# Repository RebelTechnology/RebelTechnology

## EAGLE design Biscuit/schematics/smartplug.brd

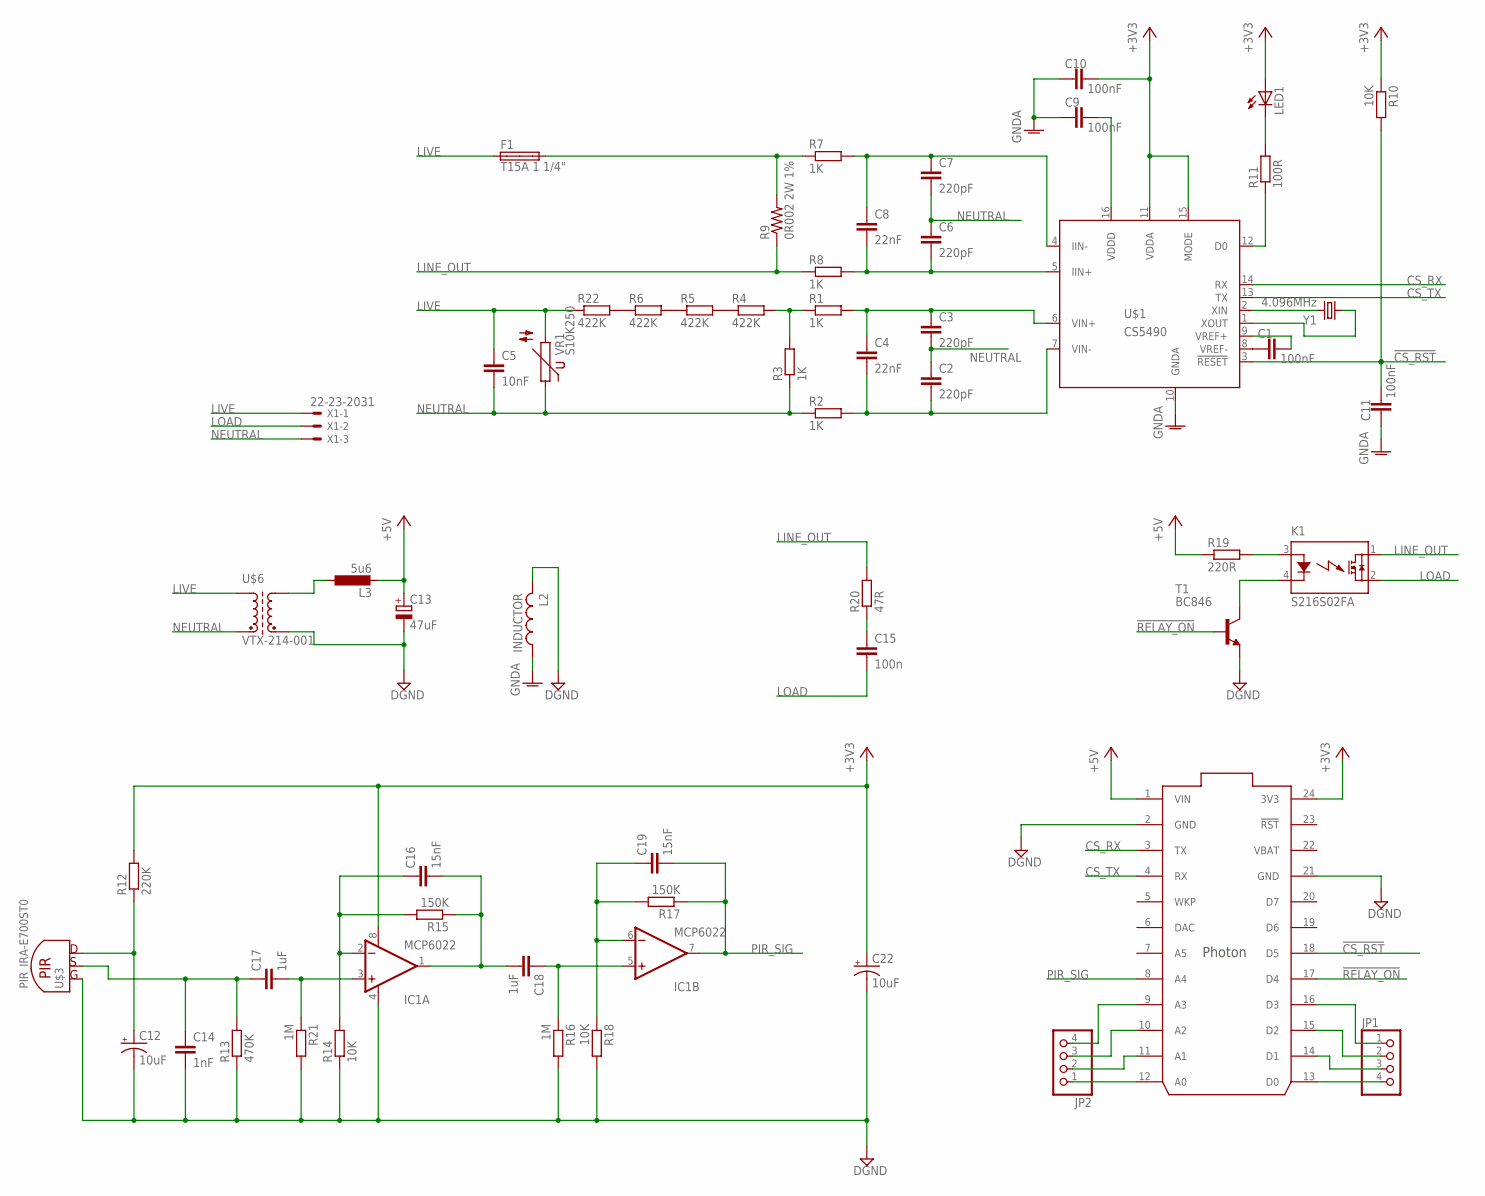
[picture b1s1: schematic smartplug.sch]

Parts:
C1, C9, C10, C11: 100nF; 0603-CAP
C2, C3, C6, C7: 220pF; 0603-CAP
C4, C8: 22nF; 0603-CAP
C5: 10nF; 0603-CAP
C12, C22: 10uF; EIA3216
C13: 47uF; 153CLV-0505
C14: 1nF; 0603-CAP
C15: 100n; C150-054X183
C16, C19: 15nF; 0603-CAP
C17, C18: 1uF; 0603-CAP
F1: T15A 1 1/4"; SH32
IC1: MCP6022; SO08
JP1, JP2: PINHD-1X4; 1X04
K1: S216S02FA; S216S02F
L2: INDUCTOR; 0603
L3: 5u6; ELLCTP
LED1: LEDCHIPLED_1206; CHIPLED_1206
R1, R2, R3, R7, R8: 1K; 0603
R4, R5, R6, R22: 422K; 0603
R9: 0R002 2W 1%; R2512
R10, R14, R18: 10K; 0603
R11: 100R; 0603
R12: 220K; 0603
R13: 470K; 0603
R15, R17: 150K; 0603
R16, R21: 1M; 0603
R19: 220R; 0603
R20: 47R; 0617V
T1: BC846; SOT23
U$1: CS5490; SOIC16N
U$2: PHOTON_WITH_HEADERS; PHOTON
U$3: PIR_IRA-E700ST0
U$6: VTX-214-001
VR1: S10K250
X1: 22-23-2031
Y1: 4.096MHz; CRYSTAL-SMD-10.5X4.8-2PIN

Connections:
!CS_RST: C11.2, R10.2, U$1.3 (!RESET), U$2.18 (D5)
!RELAY_ON: T1.1 (B), U$2.17 (D4)
+3V3: C10.2, C22.A (+), IC1.8 (V+), LED1.A, R10.1, R12.2, U$1.11 (VDDA), U$1.15 (MODE), U$2.24 (3V3)
+5V: C13.+, L3.2, R19.1, U$2.1 (VIN)
CS_RX: U$1.14 (RX), U$2.3 (TX)
CS_TX: U$1.13 (TX), U$2.4 (RX)
DGND: C12.C (-), C13.-, C14.2, C22.C (-), IC1.4 (V-), L2.2, R13.1, R14.1, R16.2, R18.2, R21.2, T1.2 (E), U$2.2 (GND), U$2.21 (GND), U$3.GND, U$6.P$V- (E2)
GNDA: C9.1, C10.1, C11.1, L2.1, U$1.10 (GNDA)
LINE_OUT: K1.1 (DS1), R8.1, R9.1, R20.2
LIVE: C5.1, F1.1A, R22.1, U$6.P$L (A1), VR1.2, X1.1
LOAD: C15.2, K1.2 (DS2), X1.2
unnamed: U$1.2 (XIN), Y1.P$2 (2)
unnamed: U$1.1 (XOUT), Y1.P$1 (1)
unnamed: C1.1, U$1.8 (VREF-)
unnamed: C1.2, U$1.9 (VREF+)
unnamed: C9.2, U$1.16 (VDDD)
unnamed: C12.A (+), R12.1, U$3.DRAIN+ (DRAIN)
unnamed: C2.2, C4.2, R2.2, U$1.7 (VIN-)
unnamed: C3.1, C4.1, R1.2, U$1.6 (VIN+)
unnamed: C6.2, C8.2, R8.2, U$1.5 (IIN+)
unnamed: C7.1, C8.1, R7.2, U$1.4 (IIN-)
unnamed: R1.1, R3.2, R4.2
unnamed: C14.1, C17.1, R13.2, U$3.SOURCE
unnamed: R4.1, R5.2
unnamed: R5.1, R6.2
unnamed: C16.1, IC1.2 (-IN), R14.2, R15.2
unnamed: R11.1, U$1.12 (D0)
unnamed: K1.4 (K), T1.3 (C)
unnamed: C17.2, IC1.3 (+IN), R21.1
unnamed: LED1.C, R11.2
unnamed: C18.1, IC1.5 (+IN), R16.1
unnamed: L3.1, U$6.P$V+ (A2)
unnamed: K1.3 (A), R19.2
unnamed: C15.1, R20.1
unnamed: C19.1, IC1.6 (-IN), R17.2, R18.1
unnamed: C16.2, C18.2, IC1.1 (OUT), R15.1
unnamed: F1.2A, R7.1, R9.2
unnamed: JP2.1, U$2.12 (A0)
unnamed: JP2.2, U$2.11 (A1)
unnamed: JP2.3, U$2.10 (A2)
unnamed: JP2.4, U$2.9 (A3)
unnamed: JP1.4, U$2.13 (D0)
unnamed: JP1.3, U$2.14 (D1)
unnamed: JP1.2, U$2.15 (D2)
unnamed: JP1.1, U$2.16 (D3)
unnamed: R6.1, R22.2
NEUTRAL: C2.1, C3.2, C5.2, C6.1, C7.2, R2.1, R3.1, U$6.P$N (E1), VR1.1, X1.3
PIR_SIG: C19.2, IC1.7 (OUT), R17.1, U$2.8 (A4)
VBAT: U$2.22 (VBAT)

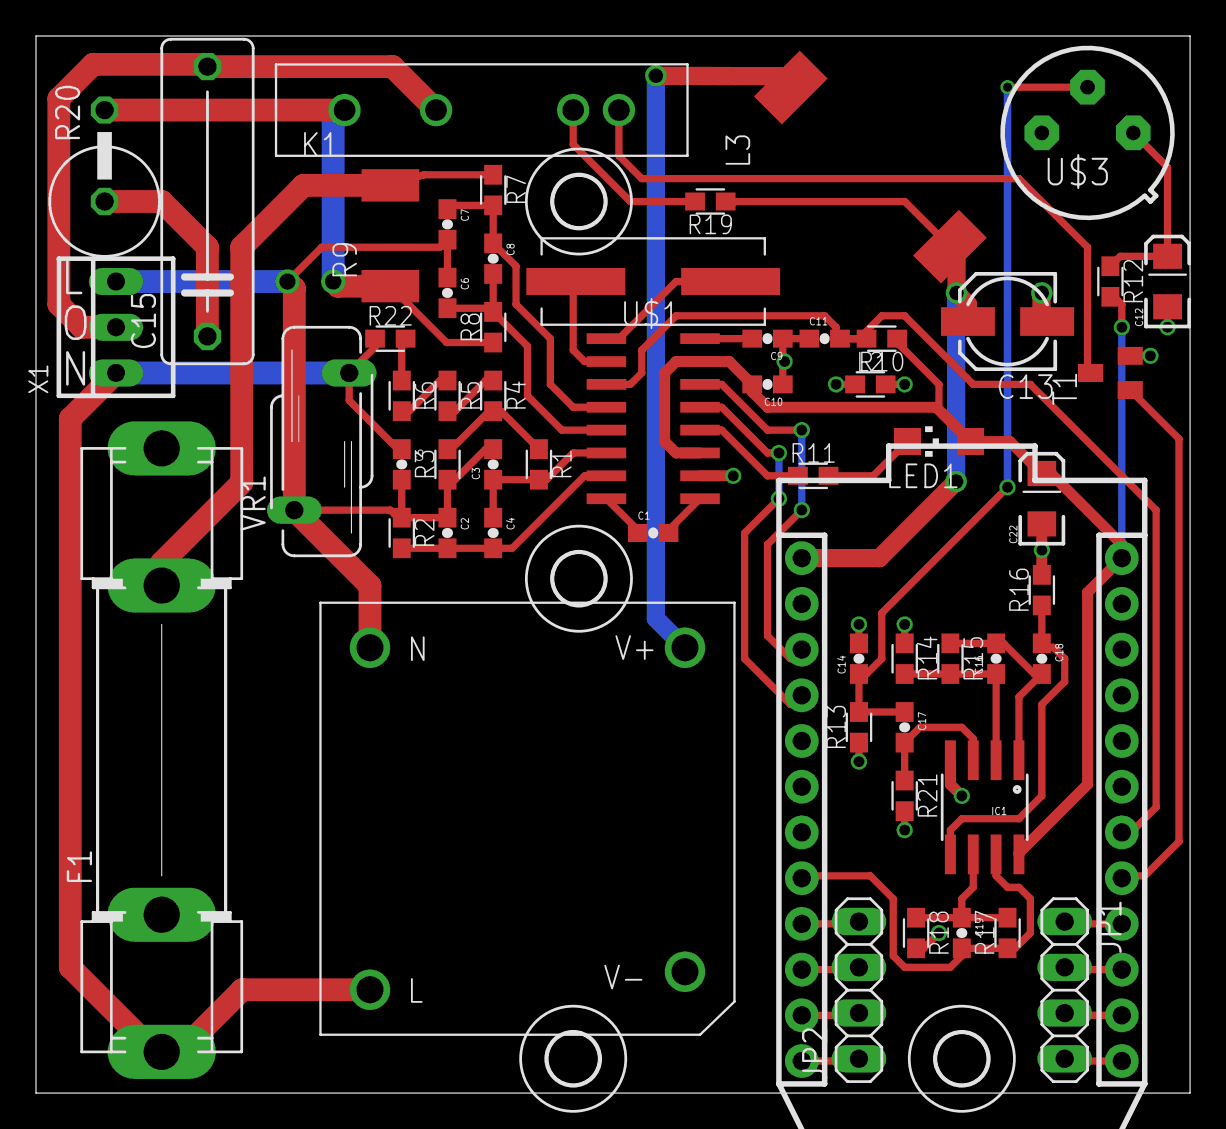
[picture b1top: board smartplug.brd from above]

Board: 2 copper layers, 64.1 x 58.7 mm, 62 parts (0 on the bottom side), 48 nets.

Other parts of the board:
U$4, U$5, U$7, U$8: 2,8

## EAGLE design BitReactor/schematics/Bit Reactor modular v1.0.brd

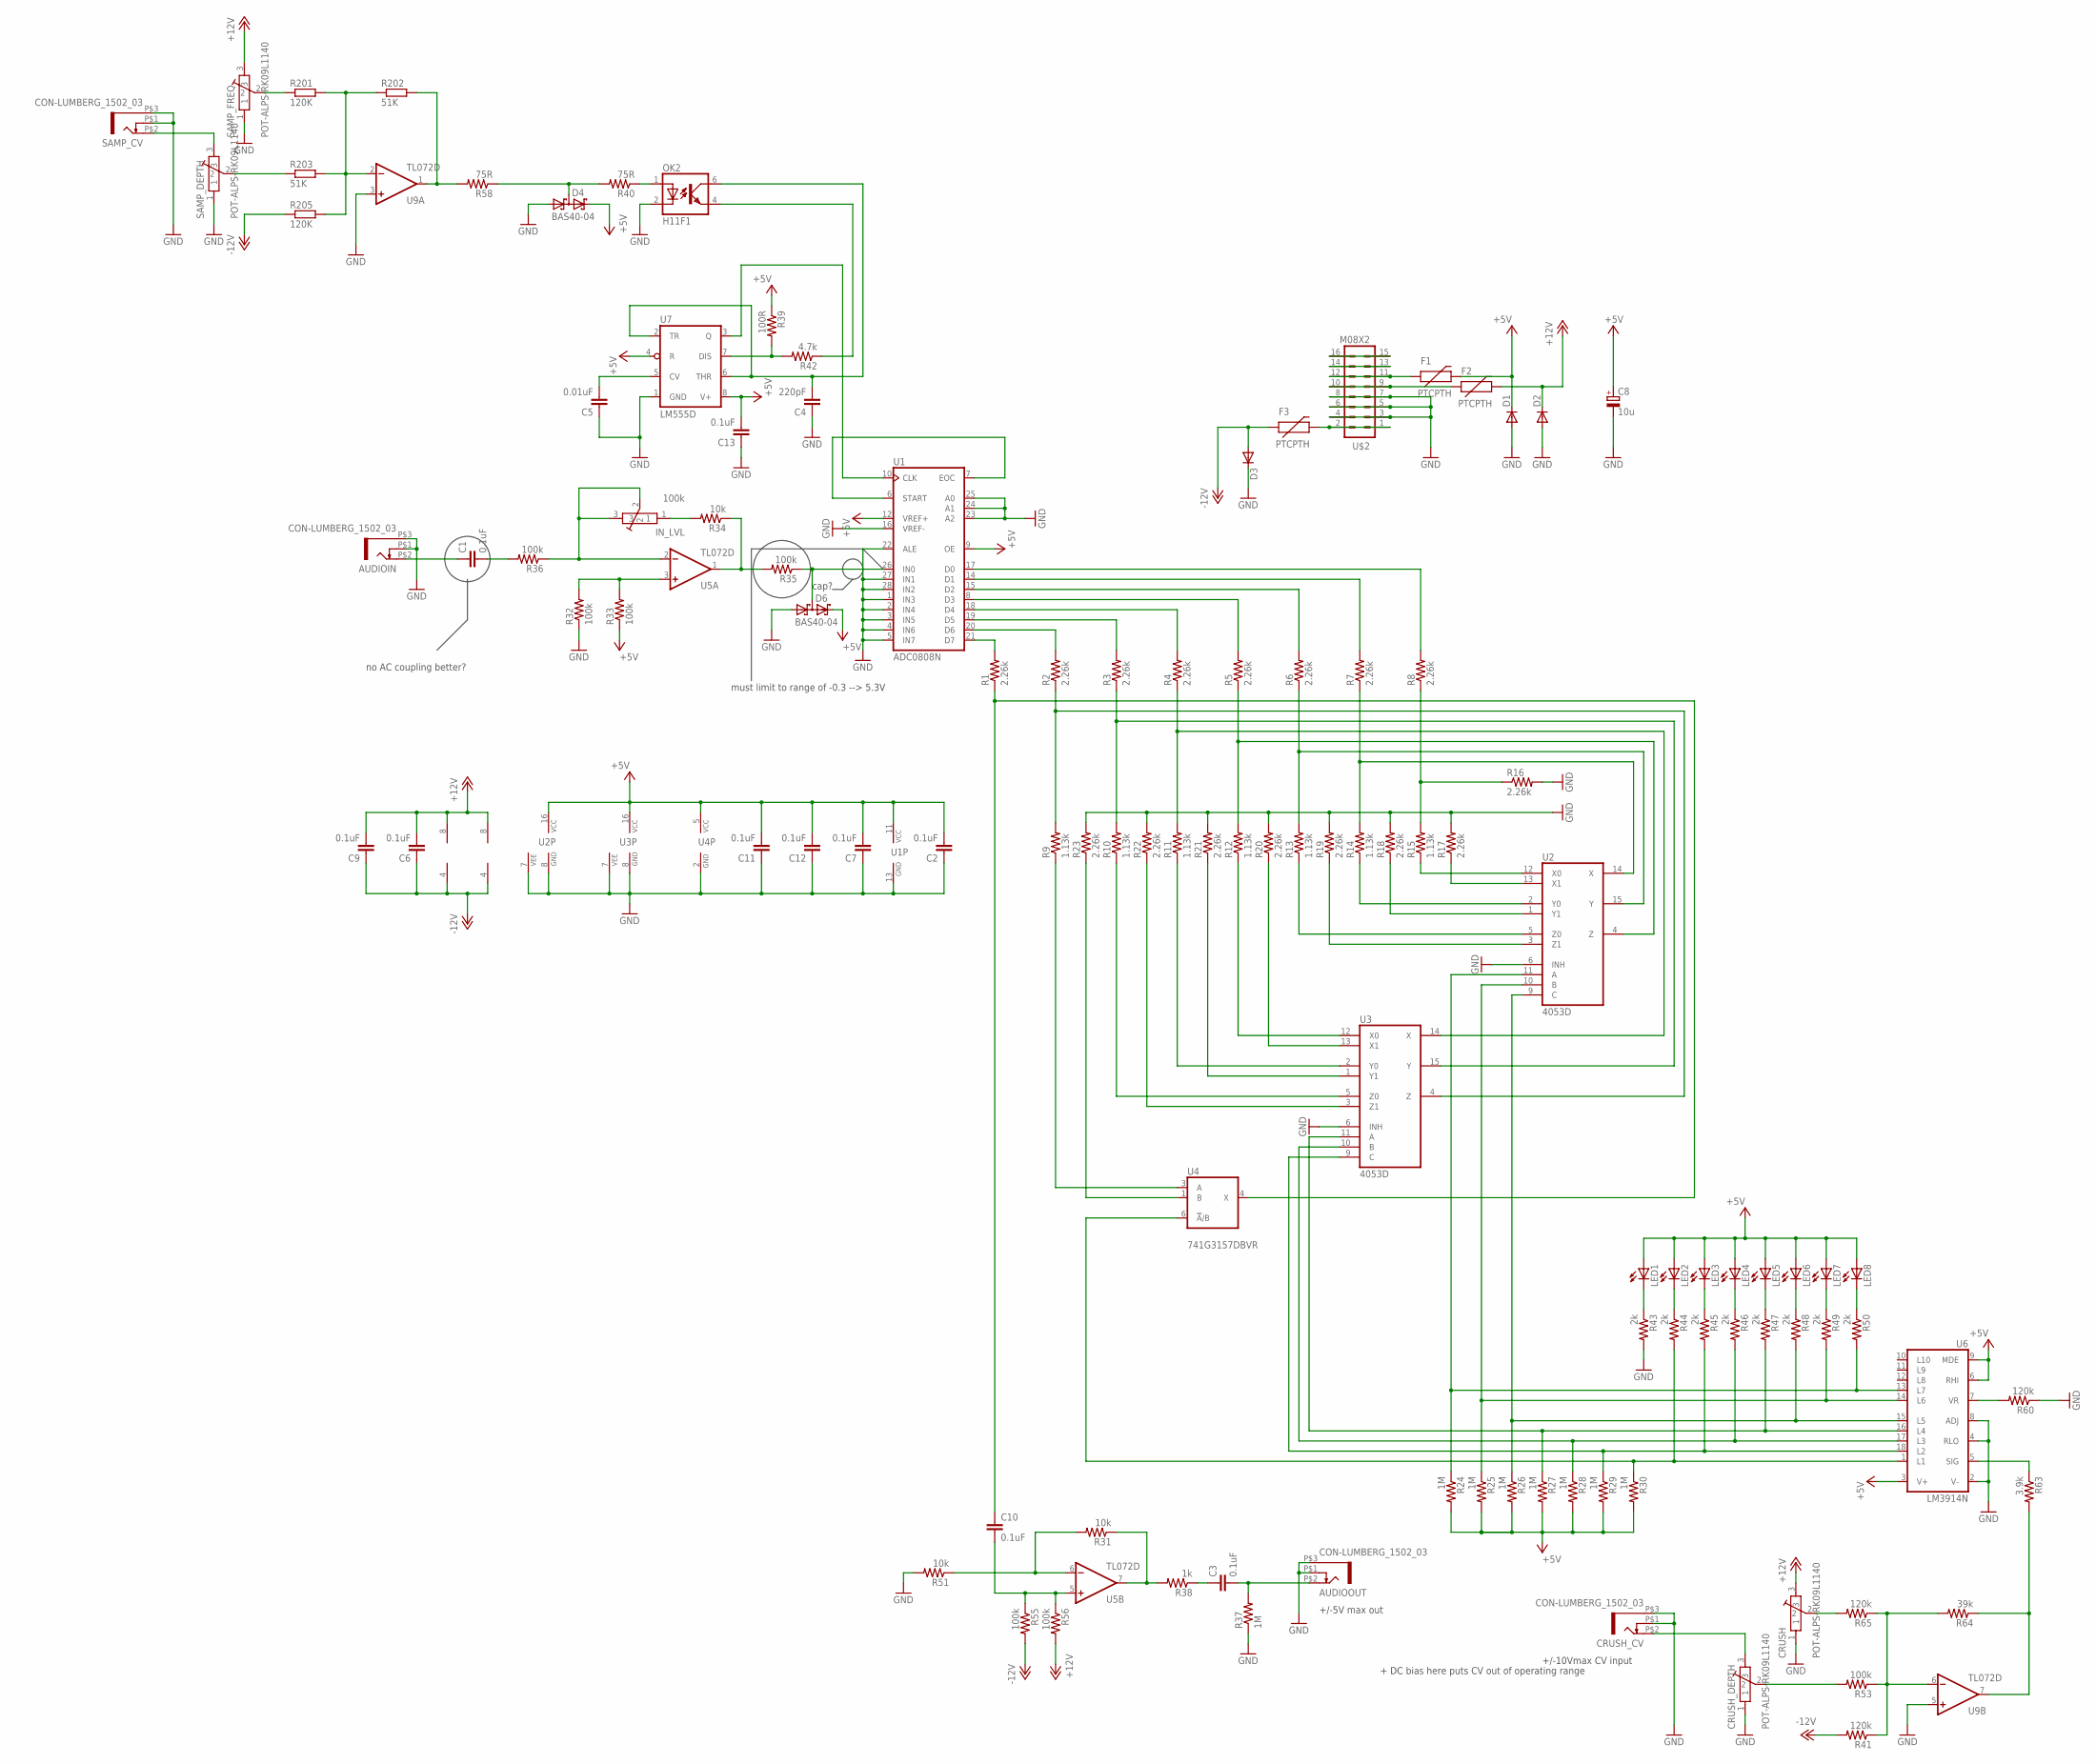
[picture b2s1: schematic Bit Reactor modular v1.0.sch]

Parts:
AUDIOIN: CON-LUMBERG_1502_03
AUDIOOUT: CON-LUMBERG_1502_03
C1, C2, C6, C7, C9, C10, C11, C12, C13: 0.1uF; C025-030X050
C3: 0.1uF; C025-025X050
C4: 220pF; C025-030X050
C5: 0.01uF; C025-030X050
C8: 10u; E5-6
CRUSH: POT-ALPS-RK09L1140
CRUSH_CV: CON-LUMBERG_1502_03
CRUSH_DEPTH: POT-ALPS-RK09L1140
D1, D2, D3: DIODE1N4001; DIODE-1N4001
D4, D6: BAS40-04; SOT23
F1, F2, F3: PTCPTH; PTC
IN_LVL: 100k; POT-ALPS-RK09L1140
LED1, LED2, LED3, LED4, LED5, LED6, LED7, LED8: LED3MM
OK2: H11F1; DIL05
R1, R2, R3, R4, R5, R6, R7, R8, R16, R17, R18, R19, R20, R21, R22, R23: 2.26k; R0805W
R9, R10, R11, R12, R13, R14, R15: 1.13k; R0805W
R24, R25, R26, R27, R28, R29, R30, R37: 1M; R0402
R31, R34, R51: 10k; 0207/10
R32, R33, R35, R36, R53, R55, R56: 100k; 0207/10
R38: 1k; 0207/10
R39: 100R; 0207/10
R40, R58: 75R; 0207/10
R41, R60, R65: 120k; 0207/10
R42: 4.7k; 0207/10
R43, R44, R45, R46, R47, R49, R50: 2k; 0207/7
R48: 2k; 0207/10
R63: 3.9k; 0207/10
R64: 39k; 0207/10
R201, R205: 120K; 0204/7
R202, R203: 51K; 0204/7
SAMP_CV: CON-LUMBERG_1502_03
SAMP_DEPTH: POT-ALPS-RK09L1140
SAMP_FREQ: POT-ALPS-RK09L1140
U1: ADC0808N; DIL28-6
U2, U3: 4053D; SO16
U4: 741G3157DBVR; DBV_R-PDSO-G6
U5, U9: TL072D; SO08
U6: LM3914N; DIL18
U7: LM555D; SO08
U$2: M08X2; 2X8

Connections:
+5V: C2.2, C7.2, C8.+, C11.2, C12.2, C13.2, D1.C, D4.2 (C2), D6.2 (C2), F1.P$2 (2), LED1.A, LED2.A, LED3.A, LED4.A, LED5.A, LED6.A, LED7.A, LED8.A, R24.2, R25.2, R26.2, R27.2, R28.2, R29.2, R30.2, R33.1, R39.1, U1.9 (OE), U1.11 (VCC), U1.12 (VREF+), U2.16 (VCC), U3.16 (VCC), U4.5 (VCC), U6.3 (V+), U6.6 (RHI), U6.9 (MDE), U7.4 (R), U7.8 (V+)
+12V: C6.2, C9.2, CRUSH.3, D2.C, F2.P$2 (2), R56.2, SAMP_FREQ.3, U5.8 (V+), U9.8 (V+)
-12V: C6.1, C9.1, D3.A, F3.P$1 (1), R41.2, R55.2, R205.1, U5.4 (V-), U9.4 (V-)
CV2IN: R63.2, R64.1, U9.7 (OUT)
GND: AUDIOIN.P$1 (4), AUDIOIN.P$3 (5), AUDIOOUT.P$1 (4), AUDIOOUT.P$3 (5), C2.1, C4.1, C5.1, C7.1, C8.-, C11.1, C12.1, C13.1, CRUSH.1, CRUSH_CV.P$1 (4), CRUSH_CV.P$3 (5), CRUSH_DEPTH.1, D1.A, D2.A, D3.C, D4.1 (A1), D6.1 (A1), OK2.2 (C), R16.2, R17.2, R18.2, R19.2, R20.2, R21.2, R22.2, R23.2, R32.1, R37.1, R43.2, R51.2, R60.1, SAMP_CV.P$1 (4), SAMP_CV.P$3 (5), SAMP_DEPTH.1, SAMP_FREQ.1, U1.1 (IN3), U1.2 (IN4), U1.3 (IN5), U1.4 (IN6), U1.5 (IN7), U1.13 (GND), U1.16 (VREF-), U1.22 (ALE), U1.23 (A2), U1.24 (A1), U1.25 (A0), U1.27 (IN1), U1.28 (IN2), U2.6 (INH), U2.7 (VEE), U2.8 (GND), U3.6 (INH), U3.7 (VEE), U3.8 (GND), U4.2 (GND), U6.2 (V-), U6.4 (RLO), U6.8 (ADJ), U7.1 (GND), U9.3 (+IN), U9.5 (+IN), U$2.3, U$2.4, U$2.5, U$2.6, U$2.7, U$2.8
unnamed: R1.2, U1.21 (D7)
unnamed: R2.2, U1.20 (D6)
unnamed: R3.2, U1.19 (D5)
unnamed: R4.2, U1.18 (D4)
unnamed: R5.2, U1.8 (D3)
unnamed: R6.2, U1.15 (D2)
unnamed: R7.2, U1.14 (D1)
unnamed: R8.2, U1.17 (D0)
unnamed: R2.1, R9.2, U3.4 (Z)
unnamed: R3.1, R10.2, U3.15 (Y)
unnamed: R4.1, R11.2, U3.14 (X)
unnamed: R5.1, R12.2, U2.4 (Z)
unnamed: R12.1, U3.12 (X0)
unnamed: R11.1, U3.2 (Y0)
unnamed: R10.1, U3.5 (Z0)
unnamed: R9.1, U4.3 (A)
unnamed: R15.1, U2.12 (X0)
unnamed: R8.1, R15.2, R16.1
unnamed: R17.1, U2.13 (X1)
unnamed: IN_LVL.1, R34.2
unnamed: R14.1, U2.2 (Y0)
unnamed: R13.1, U2.5 (Z0)
unnamed: R18.1, U2.1 (Y1)
unnamed: R19.1, U2.3 (Z1)
unnamed: R20.1, U3.13 (X1)
unnamed: R21.1, U3.1 (Y1)
unnamed: R22.1, U3.3 (Z1)
unnamed: C10.1, R1.1, U4.4 (X)
unnamed: OK2.1 (A), R40.1
unnamed: U$2.13, U$2.14
unnamed: R30.1, R44.2, U4.6 (!A!/B), U6.1 (L1)
unnamed: R29.1, R45.2, U3.9 (C), U6.18 (L2)
unnamed: R28.1, R46.2, U3.10 (B), U6.17 (L3)
unnamed: R27.1, R47.2, U3.11 (A), U6.16 (L4)
unnamed: R26.1, R48.2, U2.9 (C), U6.15 (L5)
unnamed: R25.1, R49.2, U2.10 (B), U6.14 (L6)
unnamed: R24.1, R50.2, U2.11 (A), U6.13 (L7)
unnamed: R34.1, R35.2, U5.1 (OUT)
unnamed: R32.2, R33.2, U5.3 (+IN)
unnamed: IN_LVL.2, IN_LVL.3, R36.1, U5.2 (-IN)
unnamed: F1.P$1 (1), U$2.11, U$2.12
unnamed: C1.2, R36.2
unnamed: R31.1, R38.2, U5.7 (OUT)
unnamed: C3.1, R38.1
unnamed: U1.6 (START), U1.7 (EOC)
unnamed: AUDIOIN.P$2 (3), C1.1
unnamed: CRUSH_DEPTH.2, R53.2
unnamed: CRUSH_CV.P$2 (3), CRUSH_DEPTH.3
unnamed: R39.2, R42.2, U7.7 (DIS)
unnamed: F2.P$1 (1), U$2.9, U$2.10
unnamed: C5.2, U7.5 (CV)
unnamed: LED1.K (C), R43.1
unnamed: U1.10 (CLK), U7.3 (Q)
unnamed: R31.2, R51.1, U5.6 (-IN)
unnamed: LED2.K (C), R44.1
unnamed: LED3.K (C), R45.1
unnamed: LED4.K (C), R46.1
unnamed: LED5.K (C), R47.1
unnamed: LED6.K (C), R48.1
unnamed: LED7.K (C), R49.1
unnamed: LED8.K (C), R50.1
unnamed: D6.3 (C1A2), R35.1, U1.26 (IN0)
unnamed: R7.1, R14.2, U2.14 (X)
unnamed: R6.1, R13.2, U2.15 (Y)
unnamed: C10.2, R55.1, R56.1, U5.5 (+IN)
unnamed: R23.1, U4.1 (B)
unnamed: F3.P$2 (2), U$2.1, U$2.2
unnamed: R201.2, R202.1, R203.2, R205.2, U9.2 (-IN)
unnamed: R201.1, SAMP_FREQ.2
unnamed: R58.2, R202.2, U9.1 (OUT)
unnamed: R203.1, SAMP_DEPTH.2
unnamed: SAMP_CV.P$2 (3), SAMP_DEPTH.3
unnamed: R60.2, U6.7 (VR)
unnamed: R63.1, U6.5 (SIG)
unnamed: R41.1, R53.1, R64.2, R65.1, U9.6 (-IN)
unnamed: D4.3 (C1A2), R40.2, R58.1
unnamed: CRUSH.2, R65.2
OUT: AUDIOOUT.P$2 (3), C3.2, R37.2
PWR_BUS: U$2.15, U$2.16
Y: OK2.4 (EMIT), R42.1
Z: C4.2, OK2.6 (COL), U7.2 (TR), U7.6 (THR)

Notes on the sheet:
+/-10Vmax CV input
+ DC bias here puts CV out of operating range
+/-5V max out
must limit to range of -0.3 --> 5.3V
cap?
no AC coupling better?

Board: 2 copper layers, 111 parts (0 on the bottom side), 86 nets, no tracks yet.

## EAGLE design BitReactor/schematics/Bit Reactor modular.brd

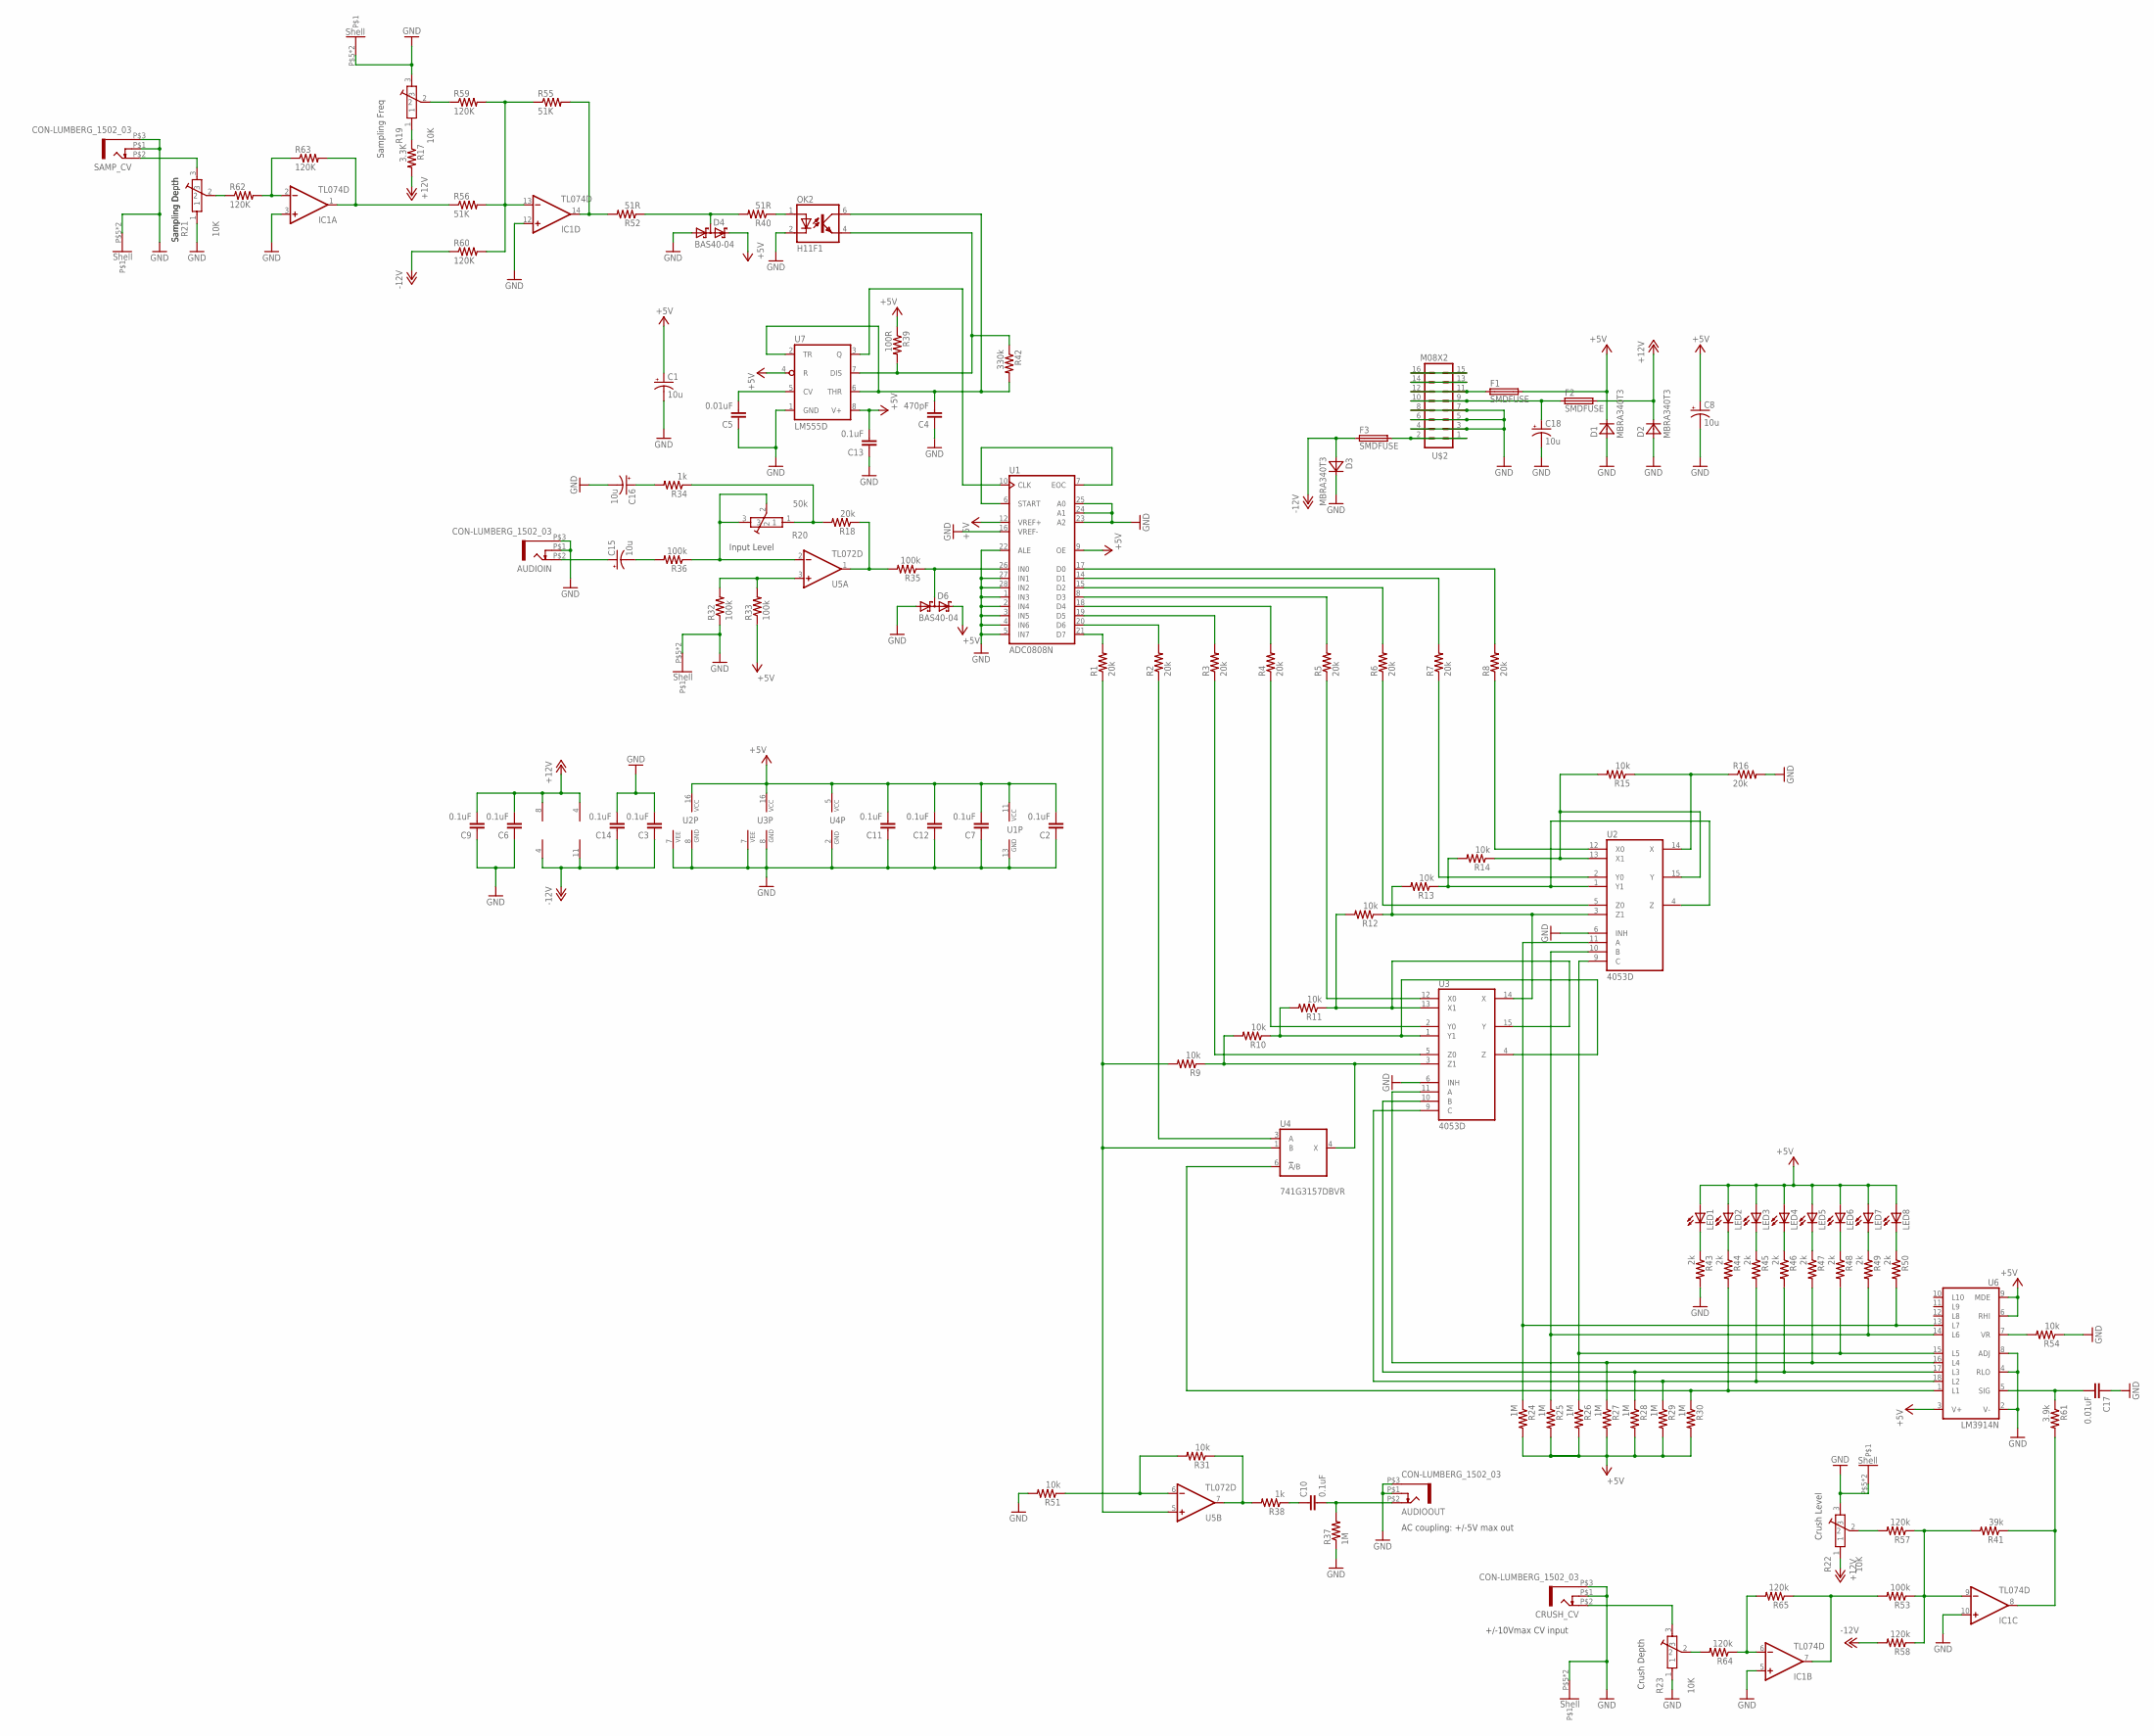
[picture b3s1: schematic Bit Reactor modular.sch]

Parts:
AUDIOIN: CON-LUMBERG_1502_03
AUDIOOUT: CON-LUMBERG_1502_03
C1, C8, C15, C16, C18: 10u; E2-5
C2, C3, C6, C7, C9, C10, C11, C12, C13, C14: 0.1uF; C0402
C4: 470pF; C0402
C5, C17: 0.01uF; C0402
CRUSH_CV: CON-LUMBERG_1502_03
D1, D2, D3: MBRA340T3; SMA
D4, D6: BAS40-04; SOT23
F1, F2, F3: SMDFUSE; 1206
IC1: TL074D; SO14
LED1, LED2, LED3, LED4, LED5, LED6, LED7, LED8: LED3MM
OK2: H11F1; DIL05
R1, R2, R3, R4, R5, R6, R7, R8, R16, R18: 20k; R0805
R9, R10, R11, R12, R13, R14, R15, R54: 10k; R0805
R17: 3.3K; R0805
R19, R21, R22, R23: 10K; POT-ALPS-RK09L1140
R20: 50k; POT-ALPS-RK09L1140
R24, R25, R26, R27, R28, R29, R30, R37: 1M; R0402
R31, R51: 10k; R0402
R32, R33, R35, R36, R53: 100k; R0402
R34, R38: 1k; R0805
R39: 100R; R1206
R40, R52: 51R; R1206
R41: 39k; R0402
R42: 330k; R0402
R43, R44, R45, R46, R47, R48, R49, R50: 2k; R0402
R55, R56: 51K; R0402
R57, R58, R64, R65: 120k; R0402
R59, R60, R62, R63: 120K; R0402
R61: 3.9k; R0402
SAMP_CV: CON-LUMBERG_1502_03
U1: ADC0808N; DIL28-6
U2, U3: 4053D; SO16
U4: 741G3157DBVR; DBV_R-PDSO-G6
U5: TL072D; SO08
U6: LM3914N; DIL18
U7: LM555D; SO08
U$2: M08X2; 2X8

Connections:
+5V: C1.+, C2.2, C7.2, C8.+, C11.2, C12.2, C13.2, D1.C, D4.2 (C2), D6.2 (C2), F1.2, LED1.A, LED2.A, LED3.A, LED4.A, LED5.A, LED6.A, LED7.A, LED8.A, R24.2, R25.2, R26.2, R27.2, R28.2, R29.2, R30.2, R33.1, R39.1, U1.9 (OE), U1.11 (VCC), U1.12 (VREF+), U2.16 (VCC), U3.16 (VCC), U4.5 (VCC), U6.3 (V+), U6.6 (RHI), U6.9 (MDE), U7.4 (R), U7.8 (V+)
+12V: C6.2, C9.2, D2.C, F2.2, IC1.4 (V+), R17.2, R22.1, U5.8 (V+)
-12V: C3.1, C14.1, D3.A, F3.1, IC1.11 (V-), R58.2, R60.1, U5.4 (V-)
CV2IN: IC1.8 (OUT), R41.1, R61.2
GND: AUDIOIN.P$1 (4), AUDIOIN.P$3 (5), AUDIOOUT.P$1 (4), AUDIOOUT.P$3 (5), C1.-, C2.1, C3.2, C4.1, C5.1, C6.1, C7.1, C8.-, C9.1, C11.1, C12.1, C13.1, C14.2, C16.-, C17.1, C18.-, CRUSH_CV.P$1 (4), CRUSH_CV.P$3 (5), D1.A, D2.A, D3.C, D4.1 (A1), D6.1 (A1), IC1.3 (+IN), IC1.5 (+IN), IC1.10 (+IN), IC1.12 (+IN), OK2.2 (C), R16.2, R19.3, R19.P$5, R19.P$6, R20.P$5, R20.P$6, R21.1, R21.P$5, R21.P$6, R22.3, R22.P$5, R22.P$6, R23.1, R23.P$5, R23.P$6, R32.1, R37.1, R43.2, R51.2, R54.1, SAMP_CV.P$1 (4), SAMP_CV.P$3 (5), U1.1 (IN3), U1.2 (IN4), U1.3 (IN5), U1.4 (IN6), U1.5 (IN7), U1.13 (GND), U1.16 (VREF-), U1.22 (ALE), U1.23 (A2), U1.24 (A1), U1.25 (A0), U1.27 (IN1), U1.28 (IN2), U2.6 (INH), U2.7 (VEE), U2.8 (GND), U3.6 (INH), U3.7 (VEE), U3.8 (GND), U4.2 (GND), U6.2 (V-), U6.4 (RLO), U6.8 (ADJ), U7.1 (GND), U$2.3, U$2.4, U$2.5, U$2.6, U$2.7, U$2.8
unnamed: R1.2, U1.21 (D7)
unnamed: R2.2, U1.20 (D6)
unnamed: R3.2, U1.19 (D5)
unnamed: R4.2, U1.18 (D4)
unnamed: R5.2, U1.8 (D3)
unnamed: R6.2, U1.15 (D2)
unnamed: R7.2, U1.14 (D1)
unnamed: R8.2, U1.17 (D0)
unnamed: R17.1, R19.1
unnamed: AUDIOIN.P$2 (3), C15.+
unnamed: C15.-, R36.2
unnamed: R13.1, R14.2, U2.1 (Y1), U2.4 (Z)
unnamed: R5.1, U3.12 (X0)
unnamed: R4.1, U3.2 (Y0)
unnamed: R3.1, U3.5 (Z0)
unnamed: R2.1, U4.3 (A)
unnamed: R8.1, U2.12 (X0)
unnamed: R21.2, R62.1
unnamed: IC1.2 (-IN), R62.2, R63.1
unnamed: R18.2, R20.1, R34.1
unnamed: R7.1, U2.2 (Y0)
unnamed: R6.1, U2.5 (Z0)
unnamed: IC1.1 (OUT), R56.1, R63.2
unnamed: R12.1, R13.2, U2.3 (Z1), U3.14 (X)
unnamed: R11.1, R12.2, U3.13 (X1), U3.15 (Y)
unnamed: R10.1, R11.2, U3.1 (Y1), U3.4 (Z)
unnamed: R9.1, R10.2, U3.3 (Z1), U4.4 (X)
unnamed: R1.1, R9.2, U4.1 (B), U5.5 (+IN)
unnamed: OK2.1 (A), R40.1
unnamed: U$2.13, U$2.14
unnamed: R30.1, R44.2, U4.6 (!A!/B), U6.1 (L1)
unnamed: R29.1, R45.2, U3.9 (C), U6.18 (L2)
unnamed: R28.1, R46.2, U3.10 (B), U6.17 (L3)
unnamed: R27.1, R47.2, U3.11 (A), U6.16 (L4)
unnamed: R26.1, R48.2, U2.9 (C), U6.15 (L5)
unnamed: R25.1, R49.2, U2.10 (B), U6.14 (L6)
unnamed: R24.1, R50.2, U2.11 (A), U6.13 (L7)
unnamed: R18.1, R35.2, U5.1 (OUT)
unnamed: R32.2, R33.2, U5.3 (+IN)
unnamed: R20.2, R20.3, R36.1, U5.2 (-IN)
unnamed: F1.1, U$2.11, U$2.12
unnamed: R23.2, R64.2
unnamed: R31.1, R38.2, U5.7 (OUT)
unnamed: C10.1, R38.1
unnamed: U1.6 (START), U1.7 (EOC)
unnamed: IC1.6 (-IN), R64.1, R65.2
unnamed: CRUSH_CV.P$2 (3), R23.3
unnamed: IC1.7 (OUT), R53.2, R65.1
unnamed: C18.+, F2.1, U$2.9, U$2.10
unnamed: C5.2, U7.5 (CV)
unnamed: LED1.K (C), R43.1
unnamed: U1.10 (CLK), U7.3 (Q)
unnamed: R31.2, R51.1, U5.6 (-IN)
unnamed: LED2.K (C), R44.1
unnamed: LED3.K (C), R45.1
unnamed: LED4.K (C), R46.1
unnamed: LED5.K (C), R47.1
unnamed: LED6.K (C), R48.1
unnamed: LED7.K (C), R49.1
unnamed: LED8.K (C), R50.1
unnamed: D6.3 (C1A2), R35.1, U1.26 (IN0)
unnamed: R14.1, R15.2, U2.13 (X1), U2.15 (Y)
unnamed: C16.+, R34.2
unnamed: F3.2, U$2.1, U$2.2
unnamed: IC1.13 (-IN), R55.1, R56.2, R59.2, R60.2
unnamed: R19.2, R59.1
unnamed: IC1.14 (OUT), R52.2, R55.2
unnamed: R21.3, SAMP_CV.P$2 (3)
unnamed: R54.2, U6.7 (VR)
unnamed: C17.2, R61.1, U6.5 (SIG)
unnamed: IC1.9 (-IN), R41.2, R53.1, R57.1, R58.1
unnamed: D4.3 (C1A2), R40.2, R52.1
unnamed: R22.2, R57.2
unnamed: R15.1, R16.1, U2.14 (X)
OUT: AUDIOOUT.P$2 (3), C10.2, R37.2
PWR_BUS: U$2.15, U$2.16
Y: OK2.4 (EMIT), R39.2, R42.1, U7.7 (DIS)
Z: C4.2, OK2.6 (COL), R42.2, U7.2 (TR), U7.6 (THR)

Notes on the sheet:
+/-10Vmax CV input
AC coupling: +/-5V max out
Sampling Depth
Sampling Freq
Input Level
Crush Depth
Crush Level

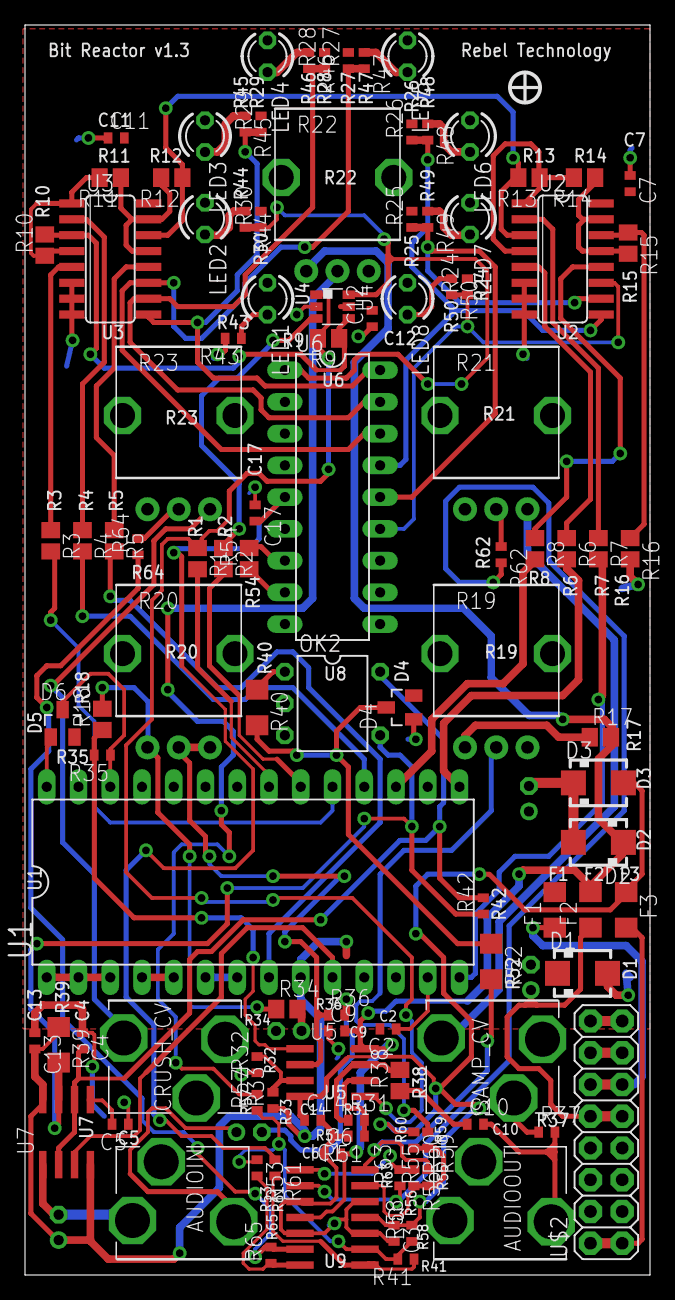
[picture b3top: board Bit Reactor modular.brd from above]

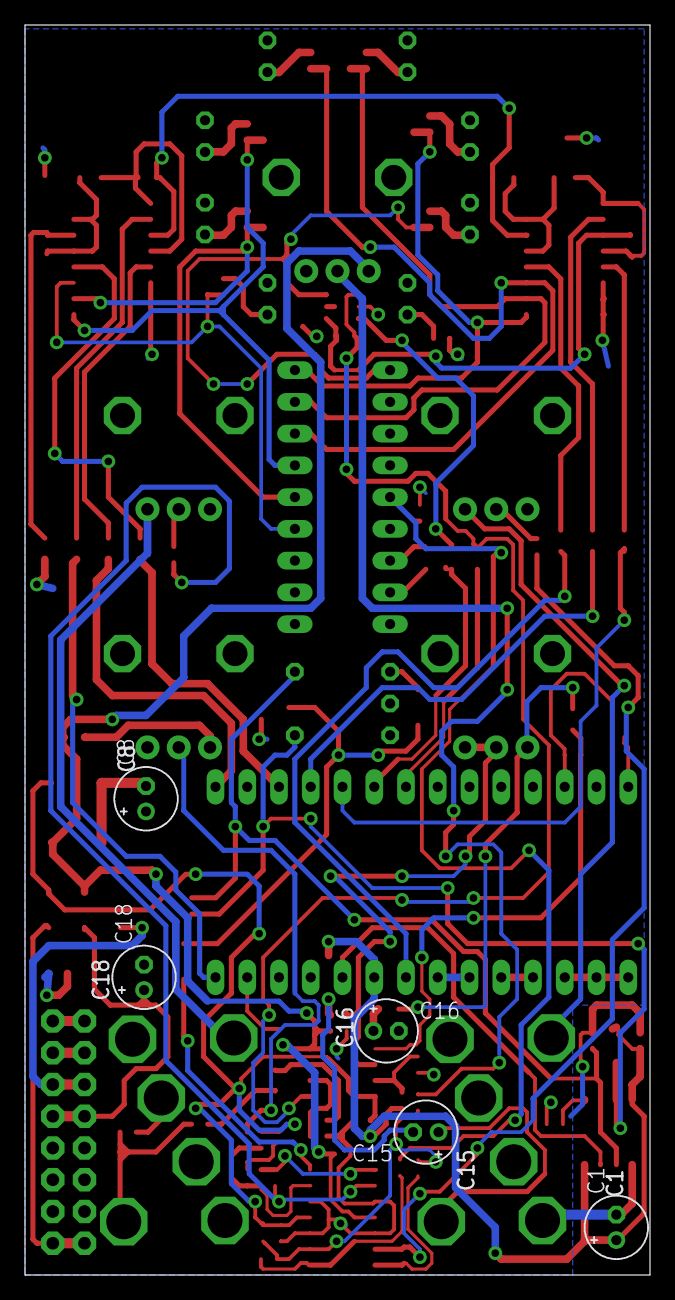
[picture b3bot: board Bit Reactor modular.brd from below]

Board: 2 copper layers, 50.0 x 100.0 mm, 113 parts (5 on the bottom side), 83 nets.

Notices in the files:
parts and their libraries:
SparkFun: Licensing: CC v3.0 Share-Alike You are welcome to use this library for commercial purposes.
